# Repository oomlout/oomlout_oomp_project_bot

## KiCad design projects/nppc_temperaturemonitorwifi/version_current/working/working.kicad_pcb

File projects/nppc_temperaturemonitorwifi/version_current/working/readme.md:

# TemperatureMonitorWIFI by nppc  
This is a harvested standardized copy of a project from github.  
The original project can be found at:  
https://github.com/nppc/TemperatureMonitorWIFI  
Please consult that link for additional, details, files, and license information.  
Note: It was auto harvested and if the original repo had more than one board file or anything out of the ordinary the files here are likely not representative.

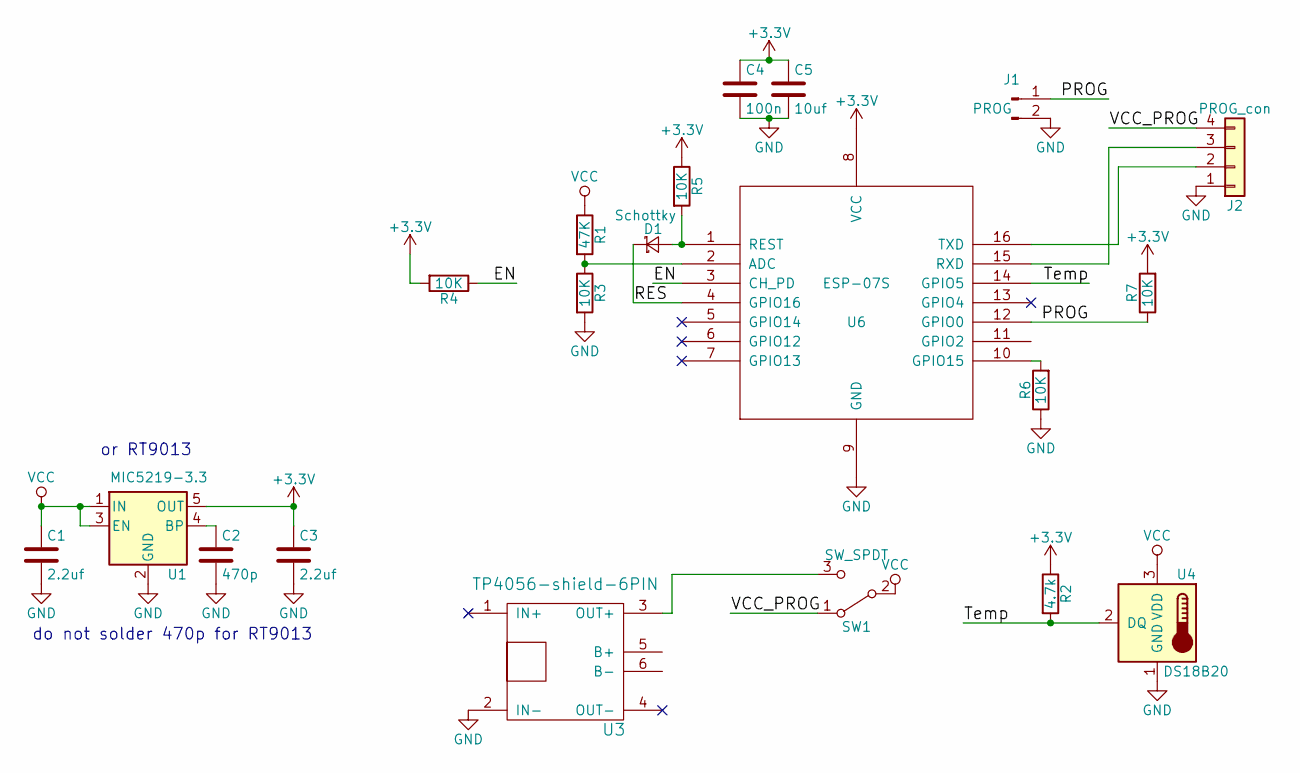
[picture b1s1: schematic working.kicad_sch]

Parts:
C1, C3: 2.2uf; C_0805
C2: 470p; C_0603
C4: 100n; C_0603
C5: 10uf; C_0805
D1: Schottky; D_SOD-523
J1: PROG; Pin_Header_Straight_1x02_Pitch2.54mm
J2: PROG_con; Pin_Header_Straight_1x04_Pitch2.54mm
R1: 47K; R_0603
R2: 4.7k; R_0603
R3, R4, R5, R6, R7: 10K; R_0603
SW1: SW_SPDT; SK12D07VG3
U1: MIC5219-3.3; SOT-23-5
U3: TP4056-shield-6PIN
U4: DS18B20; TO-92_Inline_Narrow_Oval
U6: ESP-07S

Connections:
+3V3: C3.1, C4.1, C5.1, R2.1, R4.2, R5.1, R7.2, U1.5 (OUT), U6.8 (VCC)
/EN: R4.1, U6.3 (CH_PD)
/PROG: J1.1, R7.1, U6.12 (GPIO0)
/RES: D1.1 (K), U6.4 (GPIO16)
/Temp: R2.2, U4.2 (DQ), U6.14 (GPIO5)
/VCC_PROG: J2.4, SW1.1 (A)
GND: C1.2, C2.2, C3.2, C4.2, C5.2, J1.2, J2.1, R3.2, R6.1, U1.2 (GND), U3.2 (IN-), U4.1 (GND), U6.9 (GND)
unnamed: C2.1, U1.4 (BP)
unnamed: D1.2 (A), R5.2, U6.1 (REST)
unnamed: J2.2, U6.16 (TXD)
unnamed: J2.3, U6.15 (RXD)
unnamed: R1.2, R3.1, U6.2 (ADC)
unnamed: R6.2, U6.10 (GPIO15)
unnamed: SW1.3 (C), U3.3 (OUT+)
VCC: C1.1, R1.1, SW1.2 (B), U1.1 (IN), U1.3 (EN), U4.3 (VDD)

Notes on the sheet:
do not solder 470p for RT9013
or RT9013

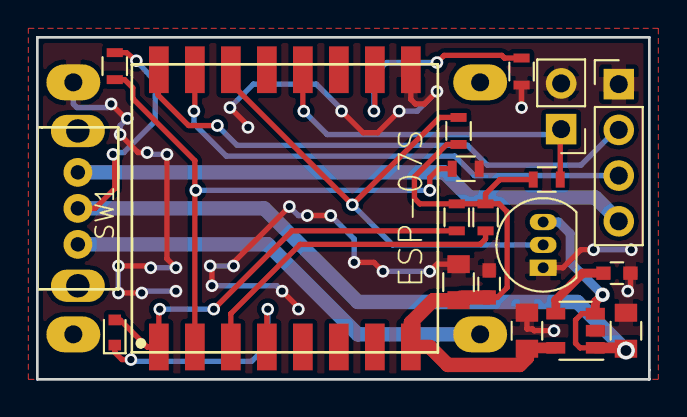
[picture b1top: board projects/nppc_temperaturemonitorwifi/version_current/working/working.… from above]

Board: 2 copper layers, 34.0 x 19.0 mm, 20 parts (1 on the bottom side), 15 nets.

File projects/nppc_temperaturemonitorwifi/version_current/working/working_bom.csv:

"Id";"Designator";"Footprint";"Quantity";"Designation";"Supplier and ref";
1;"U3";"TP4056-shield-6PIN";1;"TP4056-shield-6PIN";;;
2;"C1,C3";"C_0805";2;"2.2uf";;;
3;"C2";"C_0603";1;"470p";;;
4;"C4";"C_0603";1;"100n";;;
5;"C5";"C_0805";1;"10uf";;;
6;"D1";"D_SOD-523";1;"Schottky";;;
7;"J1";"Pin_Header_Straight_1x02_Pitch2.54mm";1;"PROG";;;
8;"J2";"Pin_Header_Straight_1x04_Pitch2.54mm";1;"PROG_con";;;
9;"R1";"R_0603";1;"47K";;;
10;"R2";"R_0603";1;"4.7k";;;
11;"R3,R4,R5,R6,R7";"R_0603";5;"10K";;;
12;"SW1";"SK12D07VG3";1;"SW_SPDT";;;
13;"U1";"SOT-23-5";1;"MIC5219-3.3";;;
14;"U4";"TO-92_Inline_Narrow_Oval";1;"DS18B20";;;
15;"U6";"ESP-07S";1;"ESP-07S";;;

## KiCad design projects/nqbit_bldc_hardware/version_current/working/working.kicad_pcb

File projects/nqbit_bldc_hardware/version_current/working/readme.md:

# bldc-hardware by nqbit  
This is a harvested standardized copy of a project from github.  
The original project can be found at:  
https://github.com/nqbit/bldc-hardware  
Please consult that link for additional, details, files, and license information.  
Note: It was auto harvested and if the original repo had more than one board file or anything out of the ordinary the files here are likely not representative.

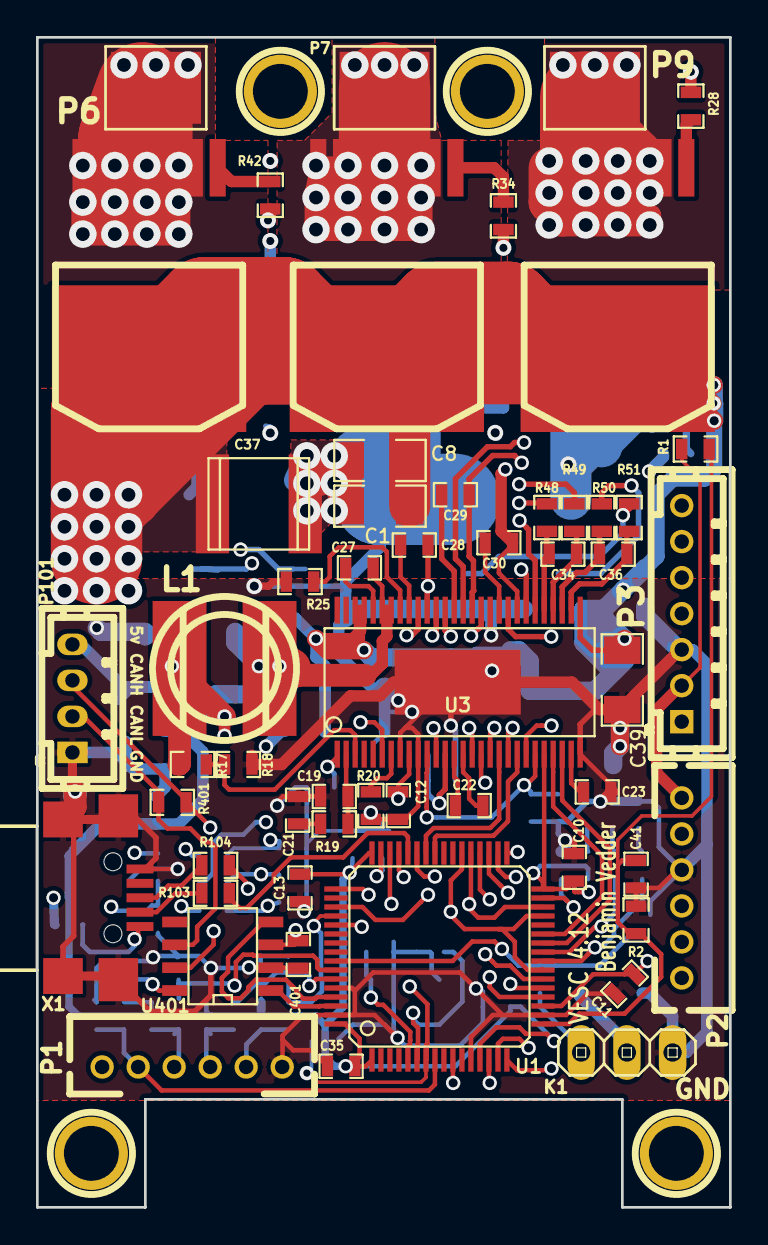
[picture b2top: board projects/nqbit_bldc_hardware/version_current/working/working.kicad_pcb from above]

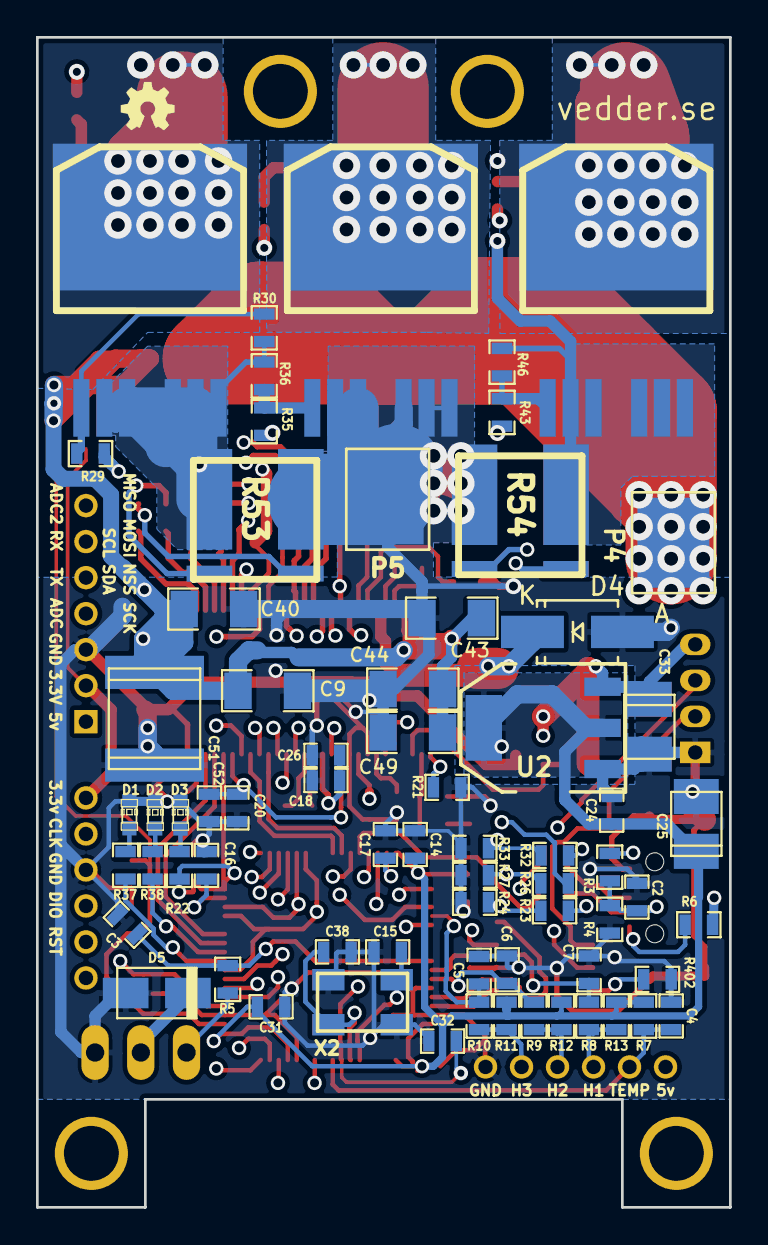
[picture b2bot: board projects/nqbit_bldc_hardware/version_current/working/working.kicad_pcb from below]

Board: 4 copper layers, 38.5 x 65.0 mm, 126 parts (68 on the bottom side), 96 nets.

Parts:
1PIN, 1PIN#2, 1PIN#3, 1PIN#4: P***; 1pin
C1, C8, C9, C39, C40, C43, C44, C49: 10u,50V; SMD-1206
C2, C3, C27, C32: 100n; SMD-0603_c
C4, C5, C6, C7: 4n7; SMD-0603_c
C10, C11, C12, C13, C14, C16, C17, C18, C20, C23, C24, C26, C31, C35, C41, C52, C401: 2.2u; SMD-0603_c
C15, C38: 15p; SMD-0603_c
C19: 120p; SMD-0603_c
C21: 6.8n; SMD-0603_c
C22: 22n; SMD-0603_c
C25, C33: 100u; c_tant_B
C28, C29, C30: 220n; SMD-0603_c
C34, C36: 2.2n; SMD-0603_c
C37: 15u,100V; c_2220
C51: 15u, 100v; c_2220
D1: GREEN; LED-0603
D2: RED; LED-0603
D3: LED; LED-0603
D4: DIODESCH; SMA_Handsoldering
D5: TVS 5V; do214ac
K1: SERVO; pinhead-1X03
L1: 22u; inductor_smd_8x5mm
P1: HALL/Encoder; MICRO_JST_6
P2: SWD; MICRO_JST_6
P3: PWR_COMM; b7b-ph-kl
P4: IN+; 1PAD_4x5mm
P5: IN-; 1PAD_4x5mm
P6: MOTOR1; 1PAD_4x5mm
P7: MOTOR2; 1PAD_4x5mm
P9: MOTOR3; 1PAD_4x5mm
P101: CANBUS; b4b-ph-kl
Q1, Q2, Q3, Q4, Q5, Q6: IRFS7530; D2PAK-7-GDS
R1: NTC 10k; SMD-0603_r
R2, R7, R8, R9, R10, R20, R402: 10k; SMD-0603_r
R3, R23, R26, R30, R32, R36, R46: 39k; SMD-0603_r
R4, R5, R11, R12, R13, R22, R24, R27, R33: 2k2; SMD-0603_r
R6: 0R; SMD-0603_r
R17: 18k; SMD-0603_r
R18: 3k3; SMD-0603_r
R19: 15k; SMD-0603_r
R21: 220k; SMD-0603_r
R25: 1M; SMD-0603_r
R28, R29, R34, R35, R42, R43: 4R7; SMD-0603_r
R37, R38, R48, R49, R50, R51: 100R; SMD-0603_r
R53, R54: SHUNT; WSLP2726
R103, R104: 22R; SMD-0603_r
R401: NI; SMD-0603_r
U1: STM32F40X_LQFP64; lqfp64_pad_mod
U2: TC2117; SOT-223
U3: DRV8302; TSSOP-56-PP
U401: SN65HVD232; SOIC-8-W
X1: MINI-USB-SHIELD-32005-201; USB-UX60R-MB-5ST
X2: 8MHz 10ppm; Crystal_5x3mm

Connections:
+5V: C33.1, D5.2, K1.2, L1.2, P1.1, P3.1, P101.4, R6.2, R17.1, U2.3
/CAN bus transceiver/CANH: P101.3, R401.1, U401.7
/CAN bus transceiver/CANL: P101.2, R401.2, U401.6
/CAN bus transceiver/CAN_RX: U1.61, U401.4
/CAN bus transceiver/CAN_TX: U1.62, U401.1
/Filters/HALL1_IN: P1.3, R8.1, R13.1
/Filters/HALL1_OUT: C7.1, R8.2, U1.58
/Filters/HALL2_IN: P1.4, R9.1, R12.1
/Filters/HALL2_OUT: C6.1, R9.2, U1.59
/Filters/HALL3_IN: P1.5, R10.1, R11.1
/Filters/HALL3_OUT: C5.1, R10.2, U1.52
/Filters/TEMP_IN: C4.2, P1.2, R7.1, U1.8
/MCU/ADC_TEMP: C41.1, R1.2, R2.1, U1.17
/MCU/AN_IN: C2.2, R3.2, R4.2, U1.10
/MCU/BR_SO1: U1.27, U3.25
/MCU/BR_SO2: U1.26, U3.26
/MCU/DC_CAL: U1.33, U3.12
/MCU/EN_GATE: U1.51, U3.16
/MCU/FAULT: U1.53, U3.6
/MCU/H1: U1.43, U3.17
/MCU/H2: U1.42, U3.19
/MCU/H3: U1.41, U3.21
/MCU/L1: U1.36, U3.18
/MCU/L2: U1.35, U3.20
/MCU/L3: U1.34, U3.22
/MCU/LED_GREEN: R37.2, U1.24
/MCU/LED_RED: R38.2, U1.25
/MCU/MISO_ADC_EXT2: P3.7, U1.22
/MCU/RX_SCL_MOSI: P3.6, U1.23, U1.29, U1.38
/MCU/SCK_ADC_EXT: P3.4, U1.21
/MCU/SENS1: R23.2, R24.2, U1.16
/MCU/SENS2: R26.2, R27.2, U1.15
/MCU/SENS3: R32.2, R33.2, U1.14
/MCU/SERVO: C3.2, R5.1, U1.57
/MCU/TX_SDA_NSS: P3.5, U1.20, U1.30, U1.37
/MCU/USB_DM: R103.1, U1.44
/MCU/USB_DP: R104.1, U1.45
/Mosfet driver/H1_LOW: Q2.S, R30.1, R36.1, R53.2, U3.44
/Mosfet driver/H1_VS: C28.1, P9.1, Q1.S, Q2.D, R32.1, U3.46
/Mosfet driver/H2_VS: C29.1, P7.1, Q3.S, Q4.D, R26.1, U3.41
/Mosfet driver/H3_LOW: Q6.S, R46.1, R54.1, U3.34
/Mosfet driver/H3_VS: C30.1, P6.1, Q5.S, Q6.D, R23.1, U3.36
/Mosfet driver/M_H1: R28.2, U3.47
/Mosfet driver/M_H2: R34.2, U3.42
/Mosfet driver/M_H3: R42.2, U3.37
/Mosfet driver/M_L1: R29.2, U3.45
/Mosfet driver/M_L2: R35.2, U3.40
/Mosfet driver/M_L3: R43.2, U3.35
/Mosfet driver/SH1_A: R48.1, R54.3
/Mosfet driver/SH1_B: R49.1, R54.4
/Mosfet driver/SH2_A: R50.1, R53.4
/Mosfet driver/SH2_B: R51.1, R53.3
GND: C1.1, C2.1, C3.1, C4.1, C5.2, C6.2, C7.2, C8.1, C9.1, C10.1, C11.1, C12.1, C13.1, C14.1, C15.2, C16.2, C17.2, C18.2, C19.1, C20.1, C21.1, C23.1, C24.2, C25.2, C26.2, C31.1, C32.1, C33.2, C35.1, C37.1, C38.2, C39.1, C40.1, C41.2, C43.2, C44.2, C49.2, C51.1, C52.1, C401.2, D1.2, D2.2, D3.2, D4.1, D5.1, K1.3, P1.6, P2.3, P3.3, P5.1, P101.1, Q4.S, R2.2, R4.1, R18.2, R20.2, R21.1, R24.1, R25.1, R27.1, R33.1, R53.1, R54.2, R402.2, U1.12, U1.18, U1.60, U1.63, U2.1, U3.8, U3.10, U3.28, U3.39, U3.57, U401.2, X1.5, X2.3
NRST: C32.2, P2.5, U1.7
unnamed: C15.1, U1.5, X2.1
unnamed: C16.1, U1.31
unnamed: C17.1, U1.47
unnamed: C18.1, C26.1, U3.13
unnamed: C19.2, R19.2, U3.2
unnamed: C20.2, C52.2, U3.11, U3.23
unnamed: C21.2, R19.1
unnamed: C22.1, U3.14
unnamed: C22.2, U3.15
unnamed: C23.2, U3.27
unnamed: C27.1, D4.2, L1.1, U3.50, U3.51
unnamed: C27.2, U3.52
unnamed: C28.2, U3.48
unnamed: C29.2, U3.43
unnamed: C30.2, U3.38
unnamed: C34.1, R48.2, U3.33
unnamed: C34.2, R49.2, U3.32
unnamed: C36.1, R50.2, U3.31
unnamed: C36.2, R51.2, U3.30
unnamed: C38.1, U1.6, X2.2
unnamed: D1.1, R37.1
unnamed: D2.1, R38.1
unnamed: D3.1, R22.1
unnamed: K1.1, R5.2
unnamed: Q1.G, R28.1
unnamed: Q2.G, R29.1, R30.2
unnamed: Q3.G, R34.1
unnamed: Q4.G, R35.1, R36.2
unnamed: Q5.G, R42.1
unnamed: Q6.G, R43.1, R46.2
unnamed: R6.1, X1.1
unnamed: R17.2, R18.1, U3.3
unnamed: R20.1, U3.7
unnamed: R21.2, U3.1
unnamed: R25.2, U3.49
unnamed: R103.2, X1.2
unnamed: R104.2, X1.3
unnamed: R402.1, U401.8
SWCLK: P2.2, U1.49
SWDIO: P2.4, U1.46
VCC: C10.2, C11.2, C12.2, C13.2, C14.2, C24.1, C25.1, C31.2, C35.2, C401.1, P2.1, P3.2, R1.1, R7.2, R11.2, R12.2, R13.2, R22.2, U1.1, U1.13, U1.19, U1.32, U1.48, U1.64, U2.2, U3.9, U3.24, U401.3
V_SUPPLY: C1.2, C8.2, C9.2, C37.2, C39.2, C40.2, C43.1, C44.1, C49.1, C51.2, P4.1, Q1.D, Q3.D, Q5.D, R3.1, U3.29, U3.53, U3.54

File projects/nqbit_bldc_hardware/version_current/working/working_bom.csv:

"Id";"Designator";"Footprint";"Quantity";"Designation";"Supplier and ref";
1;"D4";"SMA_Handsoldering";1;"DIODESCH";;;
2;"P1";"MICRO_JST_6";1;"HALL/Encoder";;;
3;"P101";"b4b-ph-kl";1;"CANBUS";;;
4;"P2";"MICRO_JST_6";1;"SWD";;;
5;"R53,R54";"WSLP2726";2;"SHUNT";;;
6;"D5";"do214ac";1;"TVS 5V";;;
7;"Q5,Q1,Q2,Q3,Q4,Q6";"D2PAK-7-GDS";6;"IRFS7530";;;
8;"X2";"Crystal_5x3mm";1;"8MHz 10ppm";;;
9;"K1";"pinhead-1X03";1;"SERVO";;;
10;"1PIN,1PIN";"1pin";2;"P***";;;
11;"G***";"oshw_silkscreen-back_3mm";1;"oshw_silkscreen-back_3mm";;;
12;"C25,C33";"c_tant_B";2;"100u";;;
13;"C37";"c_2220";1;"15u,100V";;;
14;"C51";"c_2220";1;"15u, 100v";;;
15;"D1";"LED-0603";1;"GREEN";;;
16;"D2";"LED-0603";1;"RED";;;
17;"D3";"LED-0603";1;"LED";;;
18;"L1";"inductor_smd_8x5mm";1;"22u";;;
19;"P4";"1PAD_4x5mm";1;"IN+";;;
20;"P5";"1PAD_4x5mm";1;"IN-";;;
21;"P6";"1PAD_4x5mm";1;"MOTOR1";;;
22;"P7";"1PAD_4x5mm";1;"MOTOR2";;;
23;"P9";"1PAD_4x5mm";1;"MOTOR3";;;
24;"U1";"lqfp64_pad_mod";1;"STM32F40X_LQFP64";;;
25;"U3";"TSSOP-56-PP";1;"DRV8302";;;
26;"1PIN,1PIN";"1pin";2;"P***";;;
27;"C1,C8,C9,C39,C40,C43,C44,C49";"SMD-1206";8;"10u,50V";;;
28;"C2,C3,C27,C32";"SMD-0603_c";4;"100n";;;
29;"C4,C5,C6,C7";"SMD-0603_c";4;"4n7";;;
30;"C10,C11,C12,C13,C14,C16,C17,C18,C20,C23,C24,C31,C35,C41,C52,C401,C26";"SMD-0603_c";17;"2.2u";;;
31;"C15,C38";"SMD-0603_c";2;"15p";;;
32;"C19";"SMD-0603_c";1;"120p";;;
33;"C21";"SMD-0603_c";1;"6.8n";;;
34;"C22";"SMD-0603_c";1;"22n";;;
35;"C28,C29,C30";"SMD-0603_c";3;"220n";;;
36;"C34,C36";"SMD-0603_c";2;"2.2n";;;
37;"R1";"SMD-0603_r";1;"NTC 10k";;;
38;"R2,R7,R8,R9,R10,R20,R402";"SMD-0603_r";7;"10k";;;
39;"R3,R23,R26,R30,R32,R36,R46";"SMD-0603_r";7;"39k";;;
40;"R4,R5,R11,R12,R13,R22,R24,R27,R33";"SMD-0603_r";9;"2k2";;;
41;"R6";"SMD-0603_r";1;"0R";;;
42;"R17";"SMD-0603_r";1;"18k";;;
43;"R18";"SMD-0603_r";1;"3k3";;;
44;"R19";"SMD-0603_r";1;"15k";;;
45;"R21";"SMD-0603_r";1;"220k";;;
46;"R25";"SMD-0603_r";1;"1M";;;
47;"R28,R29,R34,R35,R42,R43";"SMD-0603_r";6;"4R7";;;
48;"R37,R38,R48,R49,R50,R51";"SMD-0603_r";6;"100R";;;
49;"R103,R104";"SMD-0603_r";2;"22R";;;
50;"R401";"SMD-0603_r";1;"NI";;;
51;"U2";"SOT-223";1;"TC2117";;;
52;"U401";"SOIC-8-W";1;"SN65HVD232";;;
53;"X1";"USB-UX60R-MB-5ST";1;"MINI-USB-SHIELD-32005-201";;;
54;"P3";"b7b-ph-kl";1;"PWR_COMM";;;

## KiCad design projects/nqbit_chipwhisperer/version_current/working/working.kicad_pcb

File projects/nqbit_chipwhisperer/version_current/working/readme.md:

# chipwhisperer by nqbit  
This is a harvested standardized copy of a project from github.  
The original project can be found at:  
https://github.com/nqbit/chipwhisperer  
Please consult that link for additional, details, files, and license information.  
Note: It was auto harvested and if the original repo had more than one board file or anything out of the ordinary the files here are likely not representative.

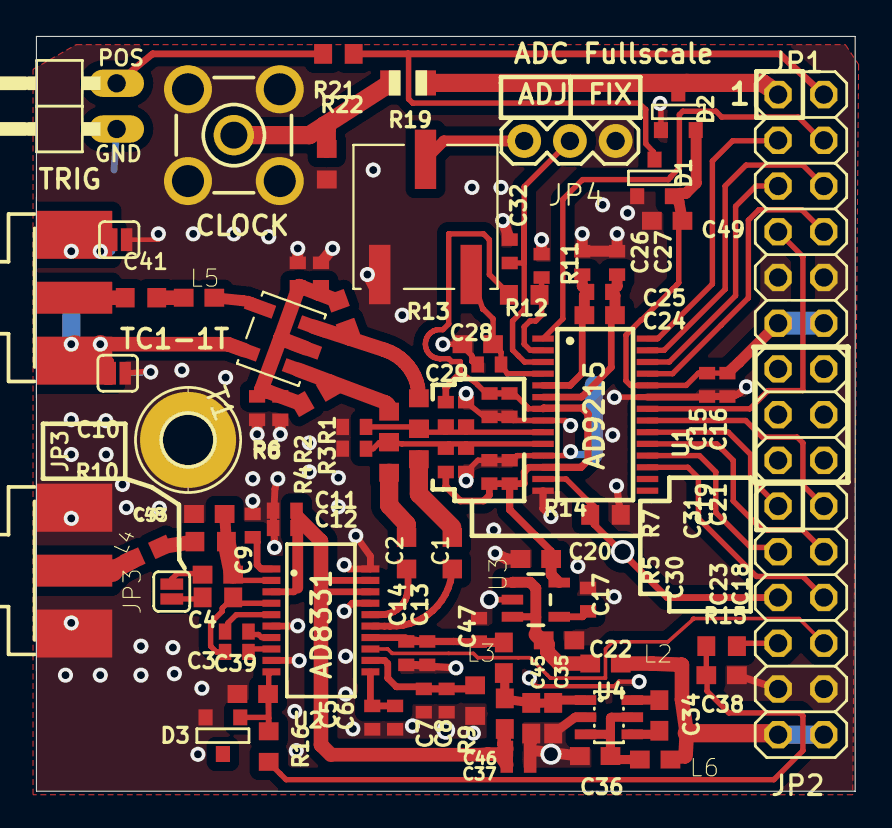
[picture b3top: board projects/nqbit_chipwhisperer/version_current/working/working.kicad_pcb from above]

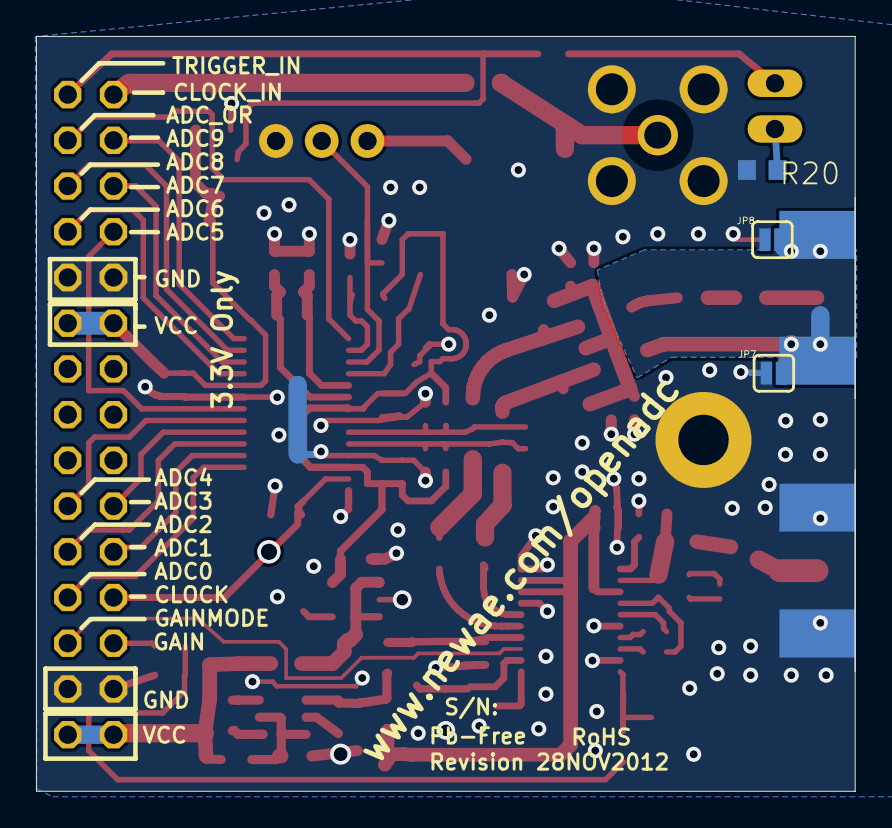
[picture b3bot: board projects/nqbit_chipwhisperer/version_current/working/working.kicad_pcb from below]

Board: 2 copper layers, 45.5 x 41.9 mm, 99 parts (3 on the bottom side), 63 nets.

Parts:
C1, C2, C33: 100nF; C0603K
C3, C4, C6, C8, C9, C11, C13, C15, C19, C23, C25, C26, C27, C29, C32, C37, C42, C44: 100nF; C0402
C5, C7, C12, C14, C40, C43: 1nF; C0402
C10: 18nF; C0603
C16, C18, C21: 10nF; C0402
C17: 10nF, COG; C0402
C20, C22, C34, C35, C36, C45: 1u; C0603
C24, C28: 10u; C0603
C30, C31: C0402
C38, C39: 1uF; C0603
C41: C0603K
C46: 1u; C0402
C47: 1uF; C0402
C48: 22pF; C0603
C49: C0603
D1, D2, D3: BAV99-7-F; SOT-23
H1: MOUNT-PAD-ROUND2.8; 2,8-PAD
JP1, JP2: 2X06
JP3, JP5, JP6, JP7, JP8: SJ_2S
JP4: JUMPER-3PTH; 1X03
JP9: 1X02_90
JP10: 2X03
L1, L2, L3, L4, L6: 120nH; 0603
L5: 0603
R1, R2: 33R, 0.5%; R0603
R3, R4: 33R; R0603
R5, R6, R7, R8, R11: 1K; R0402
R9: 10K; R0603
R10: 274R; R0603
R12: 2K; R0603
R13: 20k; 3361P
R14, R20, R21, R22: R0603
R15, R16: 2k2; R0603
R17, R18: 36R, 0.5%; R0603
R19: R0805
T1: TC1-1T; AT224-1A
U1: AD9215BRUZ; TSSOP28
U2: AD8331; QSOP20
U3: LP3985IM5-3.0; SOT23-5
U4: LTC3200ES6; SOT23-6L
X1, X2: SMA-142-0711-821/826; J502-ND-142-0711-821_826
X3: BU-SMA-V

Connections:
+3V3: C15.1, C16.1, C49.1, D1.2, D2.2, JP1.11, JP1.12, JP2.11, JP2.12, L2.1, L6.2, U1.24
+5V: C35.2, C45.2, L1.1, L3.1, U4.1
ADC0: JP2.6, U1.17
ADC1: JP2.3, U1.18
ADC2: JP2.4, U1.19
ADC3: JP2.1, U1.20
ADC4: JP2.2, U1.21
ADC5: JP1.7, U1.22
ADC6: JP1.8, U1.25
ADC7: JP1.5, U1.26
ADC8: JP1.6, U1.27
ADC9: JP1.3, U1.28
ADC_CLK: JP2.5, R14.2, U1.13
ADC_OR: JP1.4, U1.1
ADC_VCC: C18.1, C19.1, C20.1, C21.1, C23.1, R5.2, R7.1, R12.2, U1.7, U1.12, U3.5
AGND: C5.2, C6.2, C7.2, C8.2, C9.1, C11.2, C12.2, C13.2, C14.2, C15.2, C16.2, C17.1, C18.2, C19.2, C20.2, C21.2, C22.2, C23.2, C26.1, C27.1, C28.1, C29.1, C30.2, C31.2, C32.2, C35.1, C36.1, C37.2, C38.2, C39.2, C40.2, C42.2, C43.1, C44.1, C45.1, C46.1, C47.2, C48.2, C49.2, D1.3, D2.3, D3.2, H1.B2,8, JP1.9, JP1.10, JP2.9, JP2.10, JP4.3, JP5.1, JP6.1, JP7.1, JP8.1, R6.2, R8.1, R9.2, R11.2, R13.1, R14.1, R20.2, R22.1, U1.8, U1.11, U1.14, U1.23, U2.6, U2.9, U2.17, U2.20, U3.2, U4.2, X1.G@1, X1.G@2, X1.G@3, X1.G@4, X3.2, X3.3, X3.4, X3.5
GAIN: JP2.7, R15.1
HILO: JP2.8, U2.13
unnamed: C31.1, R1.1, R3.2, R7.2, R8.2, U1.9
unnamed: JP4.1, R13.2
unnamed: C1.2, R3.1
unnamed: C2.2, R4.1
unnamed: C4.2, U2.5
unnamed: C2.1, U2.16
unnamed: C1.1, U2.15
unnamed: C4.1, U2.7
unnamed: C3.2, U2.8
unnamed: C3.1, R10.2, U2.4
unnamed: C5.1, C6.1, U2.11
unnamed: C7.1, C8.1, R9.1, U2.12
unnamed: C9.2, U2.1
unnamed: C10.2, JP3.1
unnamed: JP3.2, R10.1
unnamed: C10.1, C33.1, C48.1, U2.2
unnamed: C17.2, U3.4
unnamed: D2.1, JP1.1, R19.2
unnamed: L4.1, X1.1
unnamed: C13.1, C14.1, C47.1, L3.2, U2.14
unnamed: C22.1, L2.2, U3.1, U3.3
unnamed: C24.1, C25.1, C26.2, U1.5
unnamed: C41.1, L5.1
unnamed: C24.2, C25.2, C27.2, U1.6
unnamed: C30.1, R2.1, R4.2, R5.1, R6.1, U1.10
unnamed: C28.2, C29.2, R13.3, U1.4
unnamed: C32.1, JP4.2, U1.3
unnamed: R11.1, R12.1, U1.2
unnamed: L5.2, T1.6
unnamed: JP5.2, JP6.2, JP7.2, JP8.2, T1.4, X2.G@1, X2.G@2, X2.G@3, X2.G@4
unnamed: R1.2, R17.2, T1.1
unnamed: C34.1, U4.4
unnamed: C34.2, U4.6
unnamed: C11.1, C12.1, C37.1, C46.2, L1.2, U2.3, U2.18, U2.19
unnamed: C38.1, R15.2, R16.1
unnamed: C39.1, D3.3, R16.2, U2.10
unnamed: R2.2, R18.1, T1.3
unnamed: C40.1, C42.1, C43.2, C44.2, R17.1, R18.2, T1.2
unnamed: R19.1, R22.2, X3.1
unnamed: JP9.1, R20.1
unnamed: JP9.2, R21.1
unnamed: C41.2, X2.1
unnamed: D1.1, JP1.2, R21.2
unnamed: C36.2, L6.1, U4.3, U4.5
unnamed: C33.2, L4.2

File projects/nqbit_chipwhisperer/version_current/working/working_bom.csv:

"Id";"Designator";"Footprint";"Quantity";"Designation";"Supplier and ref";
1;"C18,C16,C21";"C0402";3;"10nF";;;
2;"C23,C37,C25,C44,C13,C3,C27,C26,C6,C15,C11,C8,C19,C29,C9,C42,C4,C32";"C0402";18;"100nF";;;
3;"C17";"C0402";1;"10nF, COG";;;
4;"C30,C31";"C0402";2;"";;;
5;"JP2,JP1";"2X06";2;"";;;
6;"C48";"C0603";1;"22pF";;;
7;"D3,D1,D2";"SOT-23";3;"BAV99-7-F";;;
8;"R11,R5,R8,R7,R6";"R0402";5;"1K";;;
9;"C34,C45,C35,C36,C22,C20";"C0603";6;"1u";;;
10;"R2,R1";"R0603";2;"33R, 0.5%";;;
11;"X3";"BU-SMA-V";1;"BU-SMA-V";;;
12;"C24,C28";"C0603";2;"10u";;;
13;"R10";"R0603";1;"274R";;;
14;"T1";"AT224-1A";1;"TC1-1T";;;
15;"L6,L2,L4,L1,L3";"0603";5;"120nH";;;
16;"C49";"C0603";1;"";;;
17;"JP5,JP6,JP3,JP8,JP7";"SJ_2S";5;"";;;
18;"R3,R4";"R0603";2;"33R";;;
19;"C39,C38";"C0603";2;"1uF";;;
20;"X1,X2";"J502-ND-142-0711-821_826";2;"SMA-142-0711-821/826";;;
21;"C33,C1,C2";"C0603K";3;"100nF";;;
22;"R18,R17";"R0603";2;"36R, 0.5%";;;
23;"R15,R16";"R0603";2;"2k2";;;
24;"R19";"R0805";1;"";;;
25;"U2";"QSOP20";1;"AD8331";;;
26;"U4";"SOT23-6L";1;"LTC3200ES6";;;
27;"H1";"2,8-PAD";1;"MOUNT-PAD-ROUND2.8";;;
28;"R9";"R0603";1;"10K";;;
29;"R14,R21,R22,R20";"R0603";4;"";;;
30;"JP4";"1X03";1;"JUMPER-3PTH";;;
31;"L5";"0603";1;"";;;
32;"C5,C7,C40,C14,C43,C12";"C0402";6;"1nF";;;
33;"C46";"C0402";1;"1u";;;
34;"JP9";"1X02_90";1;"";;;
35;"R13";"3361P";1;"20k";;;
36;"U3";"SOT23-5";1;"LP3985IM5-3.0";;;
37;"U1";"TSSOP28";1;"AD9215BRUZ";;;
38;"C47";"C0402";1;"1uF";;;
39;"C10";"C0603";1;"18nF";;;
40;"C41";"C0603K";1;"";;;
41;"JP10";"2X03";1;"";;;
42;"R12";"R0603";1;"2K";;;

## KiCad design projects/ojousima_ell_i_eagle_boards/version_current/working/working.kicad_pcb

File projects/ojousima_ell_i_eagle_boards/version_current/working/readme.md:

# ELL-i-Eagle-Boards by ojousima  
This is a harvested standardized copy of a project from github.  
The original project can be found at:  
https://github.com/ojousima/ELL-i-Eagle-Boards  
Please consult that link for additional, details, files, and license information.  
Note: It was auto harvested and if the original repo had more than one board file or anything out of the ordinary the files here are likely not representative.

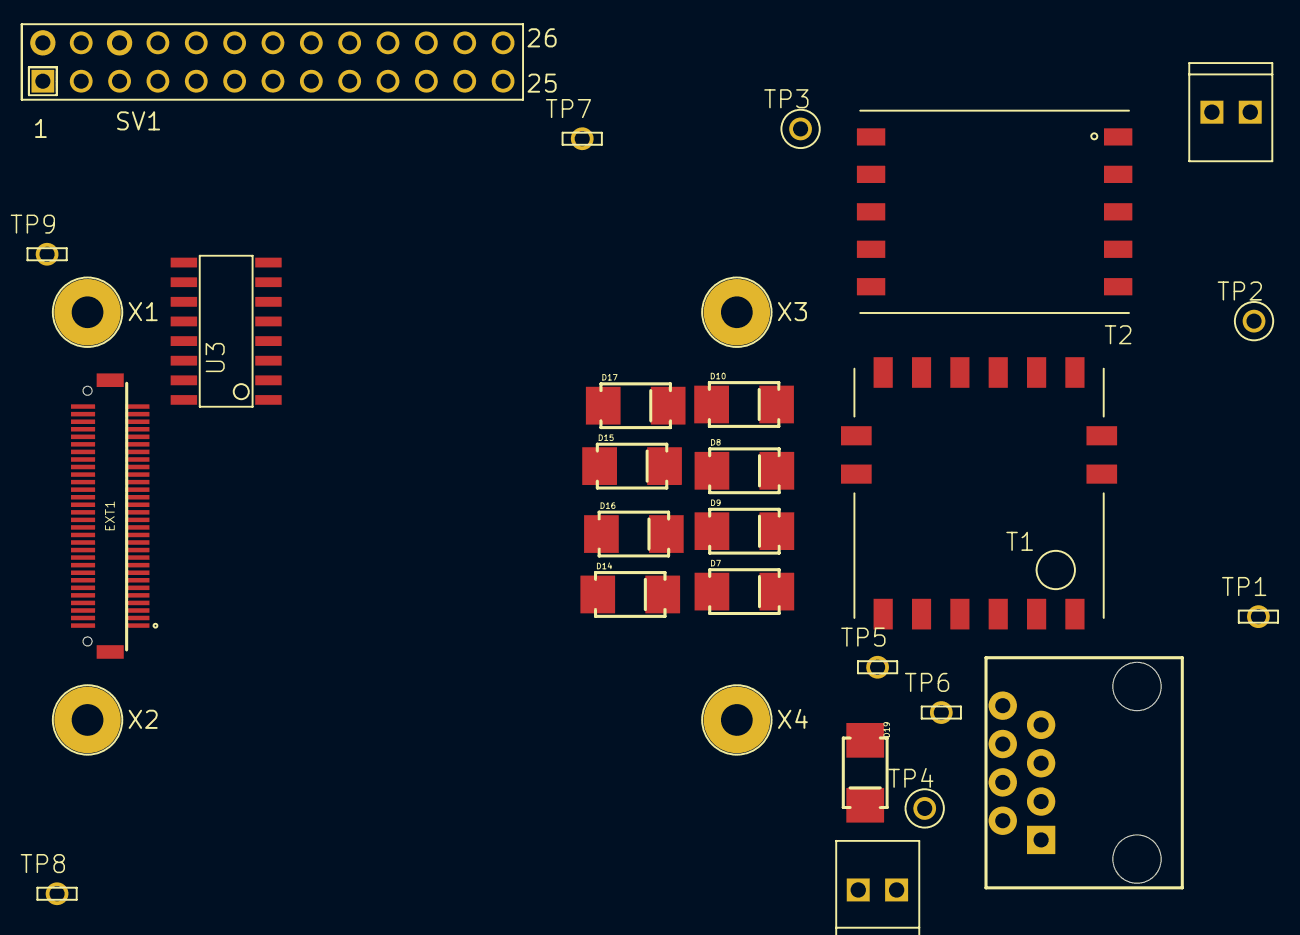
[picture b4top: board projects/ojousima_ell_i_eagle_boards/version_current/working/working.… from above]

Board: 2 copper layers, 31 parts (0 on the bottom side), 14 nets, no tracks yet.

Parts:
D7, D8, D9, D10, D14, D15, D16, D17, D19: B2100; DIODE-B2100
EXT1: DF12-ELLI-HEADER-TOP; DF12(4.0)-60DP-0.5V
J3, J4: M022.54MM; 1X02_2.54_SCREWTERM
OUTLINE1: RASPBERRY-OUTLINE; RASPBERRYPI-SHIELD-OUTLINE
SV1: RASPBERRY-CONNECTOR; RASPBERRYPI-SHIELD-CONNECTOR
T1: Coilcraft 230NL; COILCRAFT-ETH1-230L
T2: FLYBACK750311689; WE_EP13_SMD_10PIN
TP1, TP5, TP6, TP7, TP8, TP9: TP_5021
TP2, TP3, TP4: TP_5000
U3: FST3257; SOIC-16-NARROW
X1, X2, X3, X4: M-BOLT-2; M2-1
X5: POE-TP-RJ45-4UCON; 4UCON-04892

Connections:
3.3V: EXT1.6, SV1.1, SV1.17
5V: EXT1.8, SV1.2, SV1.4
GND: EXT1.12, EXT1.14, SV1.6, SV1.9, SV1.14, SV1.20, SV1.25, U3.8
unnamed: T1.10, X5.2
unnamed: T1.9, X5.1
unnamed: T1.13, X5.3
unnamed: T1.14, X5.6
unnamed: D7.C, D8.C, D9.C, D10.C
unnamed: D14.A, D15.A, D16.A, D17.A
unnamed: X5.7, X5.8
POE_A+: D7.A, D14.C
POE_A-: D8.A, D15.C, T1.12
POE_B+: D10.A, D17.C, X5.4, X5.5
POE_B-: D9.A, D16.C

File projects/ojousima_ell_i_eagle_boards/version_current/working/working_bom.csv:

"Id";"Designator";"Footprint";"Quantity";"Designation";"Supplier and ref";
1;"TP2,TP3,TP4";"TP_5000";3;"";;;
2;"D19,D17,D10,D8,D15,D9,D14,D7,D16";"DIODE-B2100";9;"B2100";;;
3;"EXT1";"DF12(4.0)-60DP-0.5V";1;"DF12-ELLI-HEADER-TOP";;;
4;"TP6,TP9,TP8,TP7,TP5,TP1";"TP_5021";6;"";;;
5;"T2";"WE_EP13_SMD_10PIN";1;"FLYBACK750311689";;;
6;"X4,X2,X3,X1";"M2-1";4;"M-BOLT-2";;;
7;"SV1";"RASPBERRYPI-SHIELD-CONNECTOR";1;"RASPBERRY-CONNECTOR";;;
8;"J3,J4";"1X02_2.54_SCREWTERM";2;"M022.54MM";;;
9;"U3";"SOIC-16-NARROW";1;"FST3257";;;
10;"T1";"COILCRAFT-ETH1-230L";1;"Coilcraft 230NL";;;
11;"X5";"4UCON-04892";1;"POE-TP-RJ45-4UCON";;;
12;"OUTLINE1";"RASPBERRYPI-SHIELD-OUTLINE";1;"RASPBERRY-OUTLINE";;;

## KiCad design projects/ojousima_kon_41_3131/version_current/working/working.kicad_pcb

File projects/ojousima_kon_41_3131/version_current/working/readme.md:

# OOMP Project  
## kon-41.3131  by ojousima  
  
oomp key: oomp_projects_flat_ojousima_kon_41_3131  
(snippet of original readme)  
  
- kon-41.3131  
Aalto university student project for constant temperature controller  
  
  full source readme at [readme_src.md](readme_src.md)  
  
source repo at: [https://github.com/ojousima/kon-41.3131](https://github.com/ojousima/kon-41.3131)  
## Board  

## Schematic  

[schematic pdf](working_schematic.pdf)  
## Images

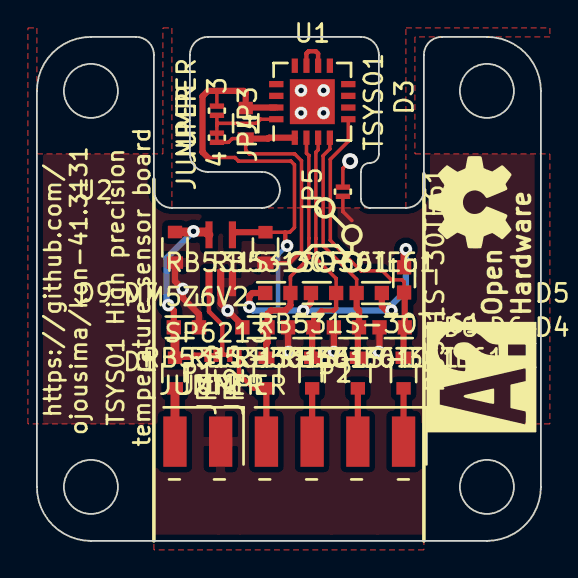
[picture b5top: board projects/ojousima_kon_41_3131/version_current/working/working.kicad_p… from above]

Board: 2 copper layers, 28.0 x 28.0 mm, 26 parts (0 on the bottom side), 14 nets.

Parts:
C1, C2: 2u2; SMD0603_WAVE
C3: 100n; SMD0603_WAVE
D1: MM5Z6V2; SOD-523
D2, D3, D4, D5, D6, D7, D8, D9: RB531S-30TE61; SOD-523
JP1, JP2, JP3, JP4, JP5: JUMPER; R_0201
P1: CONN_01X02; Pin_Header_Angled_SMD_1x02
P2: CONN_01X04; Pin_Header_Angled_SMD_1x04
R1, R2, R3, R4, R5: 220; SMD0603_WAVE
U1: TSYS01; QFN-16-1EP_4x4mm_Pitch0.65mm
U2: SP6213; SC70-6_Handsoldering

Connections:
+3V3: C2.1, C3.1, D3.2, D5.2, D7.2, D9.2, JP3.1, U1.15, U2.4
/CS: JP2.2, P2.4, R2.1
/EN: D8.2, D9.1, R2.2, U1.2
/MISO: P2.1, R5.1
/MOSI: P2.2, R4.1
/PAD: JP5.2, U1.17
/SCLK: P2.3, R3.1
/Vin: C1.1, D1.2, JP1.1, JP1.2, JP2.1, R1.1, U2.1, U2.5
GNDA: C1.2, C2.2, C3.2, D1.1, D2.1, D4.1, D6.1, D8.1, JP3.2, JP4.1, JP4.2, JP5.1, P1.1, U1.1, U1.16, U2.2, U2.3
unnamed: D2.2, D3.1, R5.2, U1.5
unnamed: D4.2, D5.1, R4.2, U1.4
unnamed: D6.2, D7.1, R3.2, U1.3
unnamed: P1.2, R1.2
unnamed: U1.10, U1.11

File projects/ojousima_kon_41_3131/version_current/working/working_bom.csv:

"Id";"Designator";"Footprint";"Quantity";"Designation";"Supplier and ref";
1;"G***,G***";"LOGO";2;"LOGO";;;
2;"P2";"Pin_Header_Angled_SMD_1x04";1;"CONN_01X04";;;
3;"U2";"SC70-6_Handsoldering";1;"SP6213";;;
4;"D1";"SOD-523";1;"MM5Z6V2";;;
5;"D2,D3,D4,D5,D6,D7,D8,D9";"SOD-523";8;"RB531S-30TE61";;;
6;"JP1,JP2,JP3,JP4,JP5";"R_0201";5;"JUMPER";;;
7;"U1";"QFN-16-1EP_4x4mm_Pitch0.65mm";1;"TSYS01";;;
8;"C1,C2";"SMD0603_WAVE";2;"2u2";;;
9;"C3";"SMD0603_WAVE";1;"100n";;;
10;"R1,R2,R3,R4,R5";"SMD0603_WAVE";5;"220";;;
11;"P1";"Pin_Header_Angled_SMD_1x02";1;"CONN_01X02";;;

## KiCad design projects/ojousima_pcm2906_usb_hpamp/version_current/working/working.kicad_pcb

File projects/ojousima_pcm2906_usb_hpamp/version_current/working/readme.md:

# OOMP Project  
## PCM2906-usb-hpamp  by ojousima  
  
oomp key: oomp_projects_flat_ojousima_pcm2906_usb_hpamp  
(snippet of original readme)  
  
PCM2906-usb-hpamp  
=================  
  
Headphone amplifier based on Texas Instruments PCM2906.  
  
Fits into Hammond enclosure 1455D602. I/O jacks are mounted into panel and wires are soldered to connectors.  
  
Future improvement:  
- All SMD-components  
- Second output to speaker amplifier, mute when headphones are detected  
  
  full source readme at [readme_src.md](readme_src.md)  
  
source repo at: [https://github.com/ojousima/PCM2906-usb-hpamp](https://github.com/ojousima/PCM2906-usb-hpamp)  
## Board  

## Schematic  

[schematic pdf](working_schematic.pdf)  
## Images

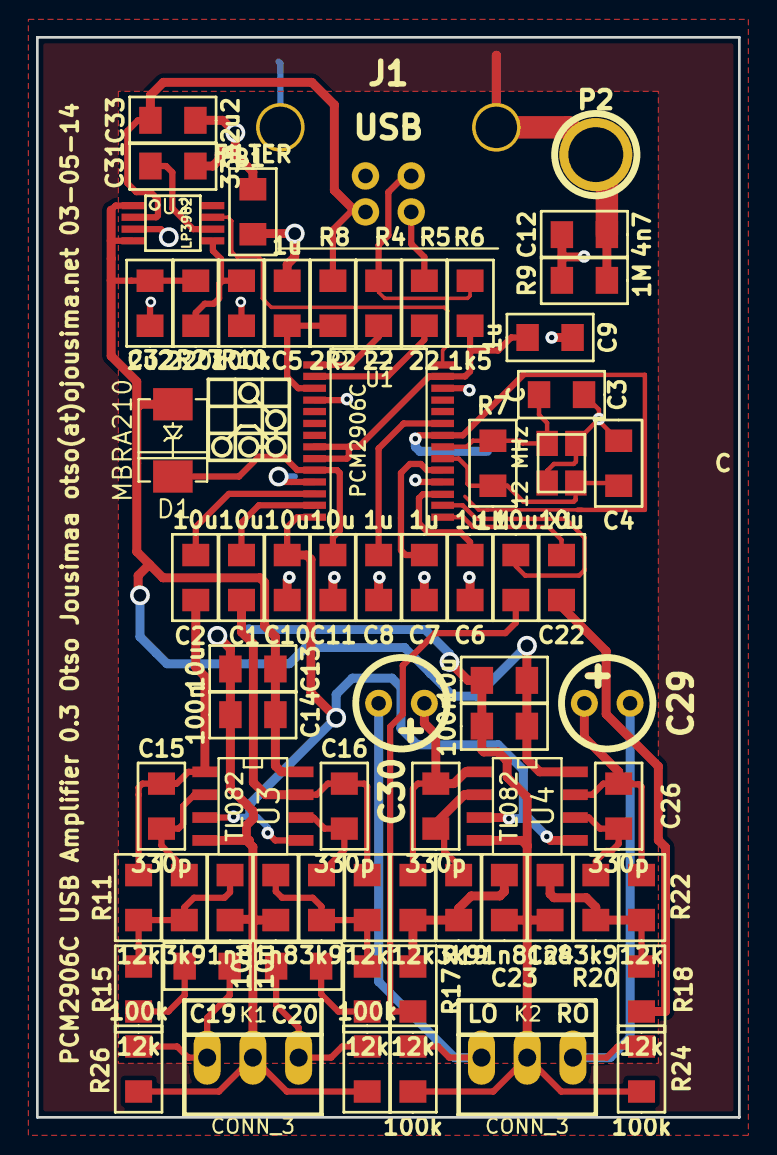
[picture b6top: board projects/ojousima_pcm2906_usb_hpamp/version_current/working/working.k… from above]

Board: 2 copper layers, 39.0 x 60.0 mm, 68 parts (0 on the bottom side), 45 nets.

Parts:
C1, C2, C10, C11, C13, C19, C20, C21, C22, C28: 10u; SMD0805_WAVE
C3, C4: C; SMD0805_WAVE
C5, C6, C7, C8, C9: 1u; SMD0805_WAVE
C12: 4n7; SMD0805_WAVE
C14, C27: 100n; SMD0805_WAVE
C15, C16, C25, C26: 330p; SMD0805_WAVE
C17, C18, C23, C24: 1n8; SMD0805_WAVE
C29, C30: 680u; Elko_vert_DM5_RM2-5
C31: 33n; SMD0805_WAVE
C32, C33: 2u2; SMD0805_WAVE
D1: MBRA210; DO-214AA(SMB)
FB1: FILTER; SMD0805_WAVE
J1: USB; USB_B
K1, K2: CONN_3; PINHEAD1-3
P2: CONN_1; 1pin
R4, R5: 22; SMD0805_WAVE
R6: 1k5; SMD0805_WAVE
R7, R9: 1M; SMD0805_WAVE
R8: 2R2; SMD0805_WAVE
R10, R23, R24, R25, R26: 100k; SMD0805_WAVE
R11, R12, R15, R16, R17, R18, R21, R22: 12k; SMD0805_WAVE
R13, R14, R19, R20: 3k9; SMD0805_WAVE
R27: 220k; SMD0805_WAVE
U1: PCM2906C; SSOP-28
U2: LP3982; SSOP-8
U3, U4: TL082; SO8E
X1: 12 MHz; crystal_FA238-TSX3225

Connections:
/ENABLE: U1.28, U2.7
/L_IN: C19.2, K1.1, R26.2
/L_OUT: C30.2, K2.1, R25.1
/R_IN: C20.2, K1.3, R23.2
/R_OUT: C29.2, K2.3, R24.1
/VBUS: C33.1, J1.1, R8.1, U2.2
/VCC: C13.1, C14.1, C27.1, C28.1, C32.1, D1.1, R27.1, U2.1, U2.4, U3.8, U4.8
/VCOM: C10.2, U1.14, U3.3, U3.5, U4.3, U4.5
/Vddi: C9.2, R6.2, U1.8, U1.9, U1.27
AGND: C13.2, C14.2, C17.2, C18.2, C23.2, C24.2, C27.2, C28.2, C31.2, C32.2, C33.2, FB1.2, K1.2, K2.2, R10.2, R23.1, R24.2, R25.2, R26.1, U2.3, U3.4, U4.4
DGND: C3.2, C4.2, C5.2, C6.1, C7.1, C8.1, C9.1, C10.1, C11.1, C12.1, FB1.1, J1.4, R9.1, U1.4, U1.11, U1.18, U1.22, U1.26, X1.3
GND: C12.2, J1.5, J1.6, P2.1, R9.2
unnamed: C1.1, C16.1, R12.1, U3.7
unnamed: C1.2, U1.13
unnamed: C2.2, U1.12
unnamed: C3.1, R7.1, U1.21, X1.1
unnamed: C4.1, R7.2, U1.20, X1.2
unnamed: C5.1, R8.2, U1.3
unnamed: C6.2, U1.17
unnamed: C7.2, U1.19
unnamed: C8.2, U1.23
unnamed: C11.2, D1.2, U1.10
unnamed: C2.1, C15.1, R11.1, U3.1
unnamed: C15.2, R13.1, U3.2
unnamed: C16.2, R14.1, U3.6
unnamed: C17.1, R11.2, R13.2, R15.1
unnamed: C18.1, R12.2, R14.2, R16.1
unnamed: C19.1, R15.2
unnamed: C20.1, R16.2
unnamed: C21.1, R17.2
unnamed: C21.2, U1.16
unnamed: C22.1, R18.2
unnamed: C22.2, U1.15
unnamed: C23.1, R17.1, R19.2, R21.2
unnamed: C24.1, R18.1, R20.2, R22.2
unnamed: C25.1, C30.1, R21.1, U4.1
unnamed: C25.2, R19.1, U4.2
unnamed: C26.1, C29.1, R22.1, U4.7
unnamed: C26.2, R20.1, U4.6
unnamed: C31.1, U2.6
unnamed: J1.2, R5.1
unnamed: J1.3, R4.1, R6.1
unnamed: R4.2, U1.1
unnamed: R5.2, U1.2
unnamed: R10.1, R27.2, U2.5

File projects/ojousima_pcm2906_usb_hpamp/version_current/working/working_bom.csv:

"Id";"Designator";"Footprint";"Quantity";"Designation";"Supplier and ref";
1;"J1";"USB_B";1;"USB";;;
2;"C1,C2,C10,C11,C13,C19,C20,C21,C22,C28";"SMD0805_WAVE";10;"10u";;;
3;"C3,C4";"SMD0805_WAVE";2;"C";;;
4;"C5,C6,C7,C8,C9";"SMD0805_WAVE";5;"1u";;;
5;"C12";"SMD0805_WAVE";1;"4n7";;;
6;"C14,C27";"SMD0805_WAVE";2;"100n";;;
7;"C15,C16,C25,C26";"SMD0805_WAVE";4;"330p";;;
8;"C17,C18,C23,C24";"SMD0805_WAVE";4;"1n8";;;
9;"C29,C30";"Elko_vert_DM5_RM2-5";2;"680u";;;
10;"C31";"SMD0805_WAVE";1;"33n";;;
11;"C32,C33";"SMD0805_WAVE";2;"2u2";;;
12;"D1";"DO-214AA(SMB)";1;"MBRA210";;;
13;"FB1";"SMD0805_WAVE";1;"FILTER";;;
14;"P2";"1pin";1;"CONN_1";;;
15;"R4,R5";"SMD0805_WAVE";2;"22";;;
16;"R6";"SMD0805_WAVE";1;"1k5";;;
17;"R7,R9";"SMD0805_WAVE";2;"1M";;;
18;"R8";"SMD0805_WAVE";1;"2R2";;;
19;"R10,R23,R24,R25,R26";"SMD0805_WAVE";5;"100k";;;
20;"R11,R12,R15,R16,R17,R18,R21,R22";"SMD0805_WAVE";8;"12k";;;
21;"R13,R14,R19,R20";"SMD0805_WAVE";4;"3k9";;;
22;"R27";"SMD0805_WAVE";1;"220k";;;
23;"U1";"SSOP-28";1;"PCM2906C";;;
24;"U2";"SSOP-8";1;"LP3982";;;
25;"U3,U4";"SO8E";2;"TL082";;;
26;"X1";"crystal_FA238-TSX3225";1;"12 MHz";;;

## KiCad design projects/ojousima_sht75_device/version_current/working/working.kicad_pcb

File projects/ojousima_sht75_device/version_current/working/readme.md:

# OOMP Project  
## SHT75-device  by ojousima  
  
oomp key: oomp_projects_flat_ojousima_sht75_device  
(snippet of original readme)  
  
- SHT75-device  
A temperature and humidity sensor project.  
  
  full source readme at [readme_src.md](readme_src.md)  
  
source repo at: [https://github.com/ojousima/SHT75-device](https://github.com/ojousima/SHT75-device)  
## Board  

## Schematic  

[schematic pdf](working_schematic.pdf)  
## Images

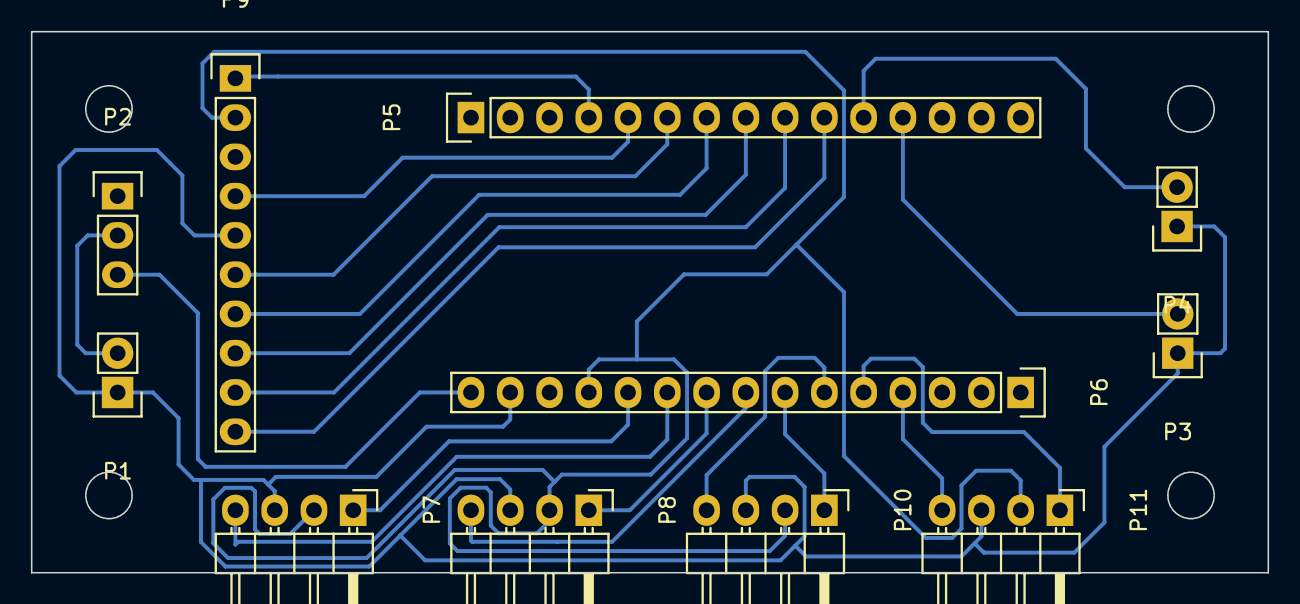
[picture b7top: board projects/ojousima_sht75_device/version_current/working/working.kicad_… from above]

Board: 4 copper layers, 80.0 x 35.0 mm, 11 parts (0 on the bottom side), 21 nets.

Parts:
P1, P3, P4: CONN_01X02; Pin_Header_Straight_1x02
P2: CONN_01X03; Pin_Header_Straight_1x03
P5, P6: CONN_01X15; Pin_Header_Straight_1x15
P7, P8, P10, P11: CONN_01X04; Pin_Header_Angled_1x04
P9: CONN_01X10; Pin_Header_Straight_1x10

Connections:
/BATT_9V: P1.2, P2.2
/BT0: P4.2, P5.11
/BT1: P3.2, P5.12
/D4: P5.7, P9.7
/D5: P5.8, P9.8
/D6: P5.9, P9.9
/D7: P5.10, P9.10
/ENABLE: P5.6, P9.6
/RESET: P5.3, P6.13
/RS: P5.5, P9.4
/SCL0: P6.5, P11.1
/SCL1: P6.7, P10.1
/SCL2: P6.9, P8.1
/SCL3: P6.11, P7.1
/SDA0: P6.4, P11.4
/SDA1: P6.6, P10.4
/SDA2: P6.8, P8.4
/SDA3: P6.10, P7.4
/VCC: P6.12, P7.2, P8.2, P9.2, P10.2, P11.2
/VIN: P2.3, P6.15
GND: P1.1, P3.1, P4.1, P5.4, P6.14, P7.3, P8.3, P9.1, P9.5, P10.3, P11.3

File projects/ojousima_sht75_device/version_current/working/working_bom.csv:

"Id";"Designator";"Footprint";"Quantity";"Designation";"Supplier and ref";
1;"P1,P3,P4";"Pin_Header_Straight_1x02";3;"CONN_01X02";;;
2;"P2";"Pin_Header_Straight_1x03";1;"CONN_01X03";;;
3;"P5,P6";"Pin_Header_Straight_1x15";2;"CONN_01X15";;;
4;"P7,P8,P10,P11";"Pin_Header_Angled_1x04";4;"CONN_01X04";;;
5;"P9";"Pin_Header_Straight_1x10";1;"CONN_01X10";;;

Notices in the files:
parts and their libraries:
Footprint Copyright (c) SparkFun under Creative Commons Share Alike License.  Not proven in production, see the discussion at the SparkFun site.
